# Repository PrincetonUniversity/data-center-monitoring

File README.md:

# A Wired Sensing Suite for Data Center Climate Monitoring

This repository contains all files related to the data center climate sensing/monitoring project built as independent work under Prof. David Wentzlaff <<wentzlaf@princeton.edu>>.

Work on this project was conducted by:

 - [Ryan O'Shea '16](http://ryanoshea.com) <<roshea@princeton.edu>> (2015-16)
 - Felix Madutsa '18 <<fmadutsa@princeton.edu>> (2015)
 - Peter de Groot '15
 - Rahul Subramanian '14
 
**For a full breakdown of the project, see the [report](/report-roshea/O'Shea_Ryan_Thesis.pdf).**

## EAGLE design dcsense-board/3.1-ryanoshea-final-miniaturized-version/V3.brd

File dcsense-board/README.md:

# Sensor Board

The `dcsense` PCB is the sensing component of the system. It is a small PCB with a TI TMP175 digital temperature sensor, DIP switches for configuring the sensor's I<sup>2</sup>C address, and a header for connecting the board to a ribbon cable via a connector. Other features include a power indicator LED and 2 decoupling capacitors.

## Layout

Reproduced below without copper pours for visibility.

## Schematic

## Addressing

The 6 switches are used to configure the address of the sensor on the bus. Beacause the switches control only 3 address pins on the TMP175 sensor (using trinary logic), not all configurations of switches will produce valid addresses. Two switches are used to configure one pin. Each pair of switches can only be set to a certain combination of values. Those pairs are (from left to right) 1 and 4, 2 and 5, 3 and 6. For a given pair of switches, the only restriction is that **both switches can't be ON simultaneously**. This is because for each pair, one switch pulls the address pin to GND and one pulls it up to V<sub>DD</sub>. Leaving both switches OFF allows the voltage of the pin to float, which a third valid option (hence trinary logic). Having both switches ON creates a voltage divider and provides a steady voltage of V<sub>DD</sub>/2 to the pin, which causes undefined behavior (and creates a leakage current that will waste unnecessary power). 

The valid address configurations are listed here, along with the decimal address values they correspond to: \[[JSON](/dcsense-board/3.1-ryanoshea-final-miniaturized-version/address-map.json)\]\[[Excel](/dcsense-board/3.1-ryanoshea-final-miniaturized-version/address-map.xlsx)\]

## History

The 3 major versions of the board are shown below.

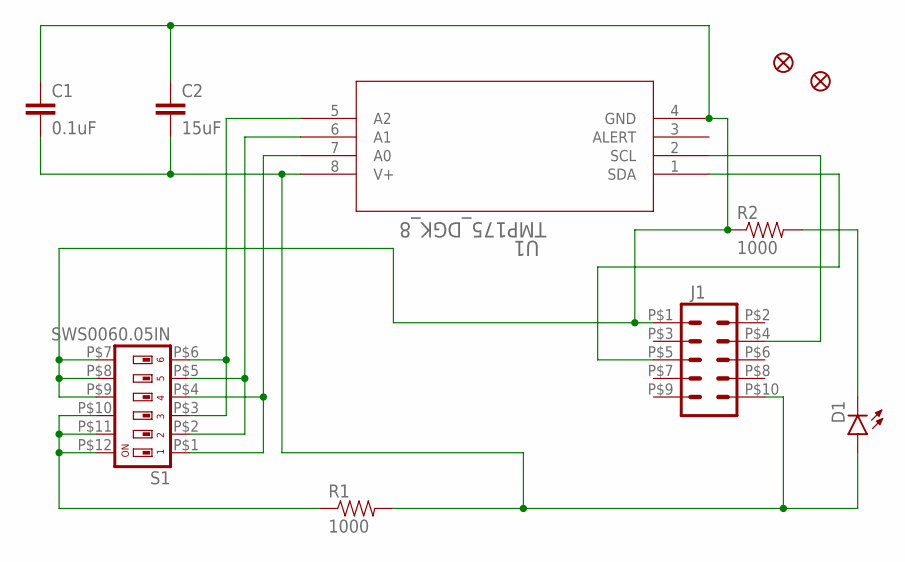
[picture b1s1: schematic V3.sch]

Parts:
C1: 0.1uF; 0805
C2: 15uF; 0805
D1: LED-BLUE1206; LED-1206
FID1, FID3: FIDUCIAL1X2; FIDUCIAL-1X2
J1: M05X22X5-UNSHROUDED_SMD; 2X5-UNSHROUDED_SMD
R1, R2: 1000; 0805
S1: SWS0060.05IN; SMS-006
U1: TMP175_DGK_8; DGK8

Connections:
A1: S1.P$2 (2), S1.P$5 (5), U1.6 (A1)
A2: S1.P$3 (3), S1.P$6 (6), U1.5 (A2)
GND: C1.1, C2.1, J1.P$1 (1), R2.1, S1.P$7 (7), S1.P$8 (8), S1.P$9 (9), U1.4 (GND)
unnamed: R1.1, S1.P$10 (10), S1.P$11 (11), S1.P$12 (12)
unnamed: S1.P$1 (1), S1.P$4 (4), U1.7 (A0)
unnamed: D1.C, R2.2
POWER: C1.2, C2.2, D1.A, J1.P$10 (10), R1.2, U1.8 (V+)
SCL: J1.P$4 (4), U1.2 (SCL)
SDA: J1.P$5 (5), U1.1 (SDA)

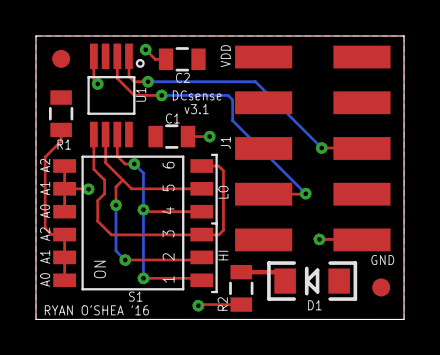
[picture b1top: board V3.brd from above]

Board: 2 copper layers, 20.4 x 15.7 mm, 10 parts (0 on the bottom side), 9 nets.

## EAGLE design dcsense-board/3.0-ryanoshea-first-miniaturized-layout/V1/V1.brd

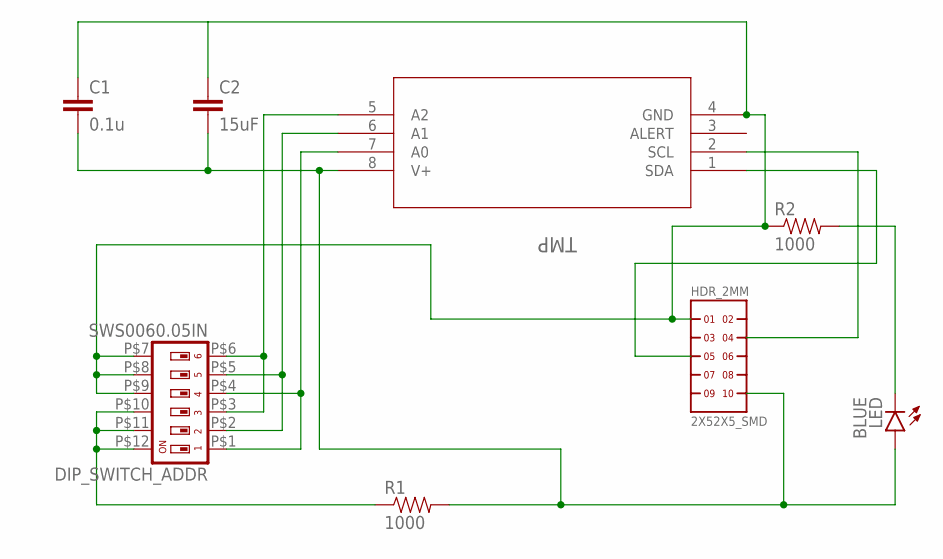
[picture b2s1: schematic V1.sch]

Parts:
C1: 0.1u; 0805
C2: 15uF; 0805-CAP
DIP_SWITCH_ADDR: SWS0060.05IN; SMS-006
HDR_2MM: 2X52X5_SMD; 2X5
LED: BLUE; LED-1206
R1, R2: 1000; 0805
TMP: TMP175_DGK_8; DGK8

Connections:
A1: DIP_SWITCH_ADDR.P$2 (2), DIP_SWITCH_ADDR.P$5 (5), TMP.6 (A1)
A2: DIP_SWITCH_ADDR.P$3 (3), DIP_SWITCH_ADDR.P$6 (6), TMP.5 (A2)
GND: C1.1, C2.1, DIP_SWITCH_ADDR.P$7 (7), DIP_SWITCH_ADDR.P$8 (8), DIP_SWITCH_ADDR.P$9 (9), HDR_2MM.P$1 (1), R2.1, TMP.4 (GND)
unnamed: C1.2, C2.2, HDR_2MM.P$10 (10), LED.A, R1.2, TMP.8 (V+)
unnamed: DIP_SWITCH_ADDR.P$10 (10), DIP_SWITCH_ADDR.P$11 (11), DIP_SWITCH_ADDR.P$12 (12), R1.1
unnamed: DIP_SWITCH_ADDR.P$1 (1), DIP_SWITCH_ADDR.P$4 (4), TMP.7 (A0)
unnamed: LED.C, R2.2
SCL: HDR_2MM.P$4 (4), TMP.2 (SCL)
SDA: HDR_2MM.P$5 (5), TMP.1 (SDA)

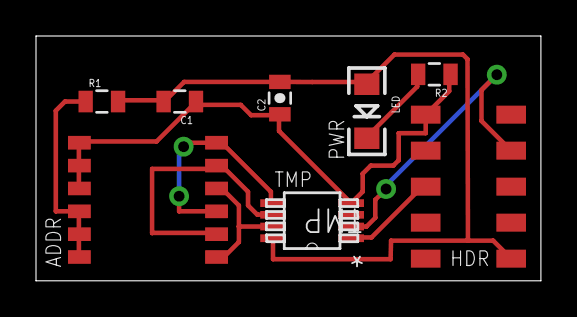
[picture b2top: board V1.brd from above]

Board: 2 copper layers, 28.1 x 13.6 mm, 8 parts (0 on the bottom side), 9 nets.

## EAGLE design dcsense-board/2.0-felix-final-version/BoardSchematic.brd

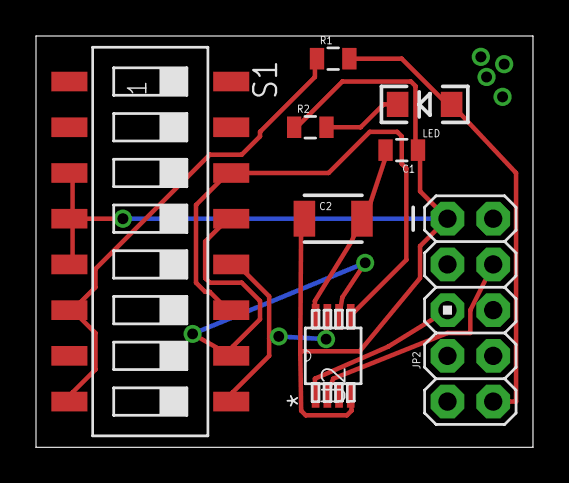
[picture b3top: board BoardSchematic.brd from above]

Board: 2 copper layers, 27.6 x 22.8 mm, 8 parts (0 on the bottom side), 10 nets.

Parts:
C1: 0.1micro; 0805
C2: 1micro; 1210
JP2: AVR_ICSP
LED: BLUE; LED-1206
R1, R2: 1000; 0805
S1: SWS008; SMS-008
U2: TMP175_DGK_8; DGK8

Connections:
unnamed: C1.2, C2.2, U2.8
unnamed: JP2.4, U2.2
unnamed: C1.1, C2.1, JP2.1, R2.1, S1.3, S1.4, S1.5, U2.4
unnamed: R1.1, S1.6, S1.8
unnamed: S1.10, S1.13, U2.6
unnamed: S1.9, S1.12, U2.7
unnamed: S1.11, S1.14, U2.5
unnamed: LED.C, R2.2
unnamed: JP2.10, LED.A, R1.2
unnamed: JP2.5, U2.1

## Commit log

2016-02-24 Init
2016-02-24 Added Felix's beaglebone python files
2016-02-24 Removed calls to DB, added print statements for temp readings
2016-02-24 Added interim report
2016-02-24 Added README
2016-02-24 Added board files from recent versions
2016-02-24 Some .gitignore changes
2016-02-24 Ignored PyCharm files
2016-02-24 Organized beaglebone controller code into old and new projects
2016-03-07 Updated board silkscreens
2016-03-17 Lockfiles
2016-03-17 Added new, simplified BeagleBone code
2016-03-17 [BB] Added error handling; added data transmission to server
2016-03-17 [Server] Added basic server to accept sensor data
2016-03-17 [Server] Added received readings tally for convenience
2016-03-17 [BB] Fixed bus 2 errors, decreased time resolution
    Also fixed error handling bugs
2016-03-18 [Server][BB] Starting saving readings to db
2016-03-18 [BRD] Fixed reference designator for header in BoM
2016-03-21 [Server] Established working server for backend and frontend
2016-03-22 [Server] Added AngularJS app with full authentication, added authentication functionality to Node server
    Built new blank AngularJS application:
    - Functional login page
    - Promise-based route authentication
    - Persistent user sessions via cookies
    - Server side authentication, with managed user DB
    - Admin page with new user registration form
2016-03-22 [Server] Fixed JSON parsing bug on logout requests
2016-03-22 Edited unix file permissions for server
2016-03-22 [Server] Added basic splash page
2016-03-23 [BB][Server] Updated controller code to send data to production server
2016-03-23 [BB] Added exception handler for failed fork()
    This solution just ignores the error. If it happens frequently, it'll
    need to be addressed a different way to avoid lost readings.
2016-03-23 [Server] Moved logout function to a directive
    So it can be used on each page without having to define a
    $scope.logout() for each page that needs a login page.
2016-03-23 [Server] Added empty dashboard page
    Made the dashboard the default page for a logged-in user
2016-03-23 [BB] Fixed issue where each bus got different timestamp
2016-03-23 [BB] Fixed issue where child processes became zombies
2016-03-24 [Server] Added some API handlers for getting readings
2016-03-26 [Server] Added working user access levels
2016-03-26 [Server] Broke out session status check to separate function
2016-03-26 [Server] Restructured session status callback to only be called if user is authorized
2016-03-26 [Server] Added authentication to one data request handler
2016-03-27 [Server] Added authentication to all requests for sensor data
2016-03-27 [Server] Added facilities & tool for managing facility owners
2016-03-28 [Server] Fixed bug allowing modifying owners on unselected facility
2016-03-28 [Server] Added admin tool to delete users
2016-03-28 [Server] Added Node.js package.json
2016-03-28 [Server] Added server app readme
2016-03-30 [Server] Limited user access to data based on facility ownership
    - Sensor data requests now check for ownership, and requests to list
    facilities return only those a user is owner of (or all if user is
    admin)
    - Added admin tool to link controllers to facilities
    - Added first parts dashboard
2016-03-30 [Server] Added code to fetch available dates for a controller on the dash
2016-03-30 [Server] Implemented readings fetching by date slider
2016-03-30 [Server] Added every-10-mins collection for readings
2016-03-30 [Server] Fixed typo
2016-03-30 [Server] Possibly fixed ReadingCounter incrementing bug
2016-03-30 [Server] Commented each server function
2016-03-30 [BB] Removed old controller code for simplicity
2016-04-02 [Server] Server header
2016-04-02 [Server] Fixed date slider on mobile
2016-04-02 [Server] Dash: facility and controller selection
2016-04-03 [Server] Tooltips and early controller name editing support
2016-04-03 [Server] Added controller renaming
2016-04-03 [Sever] Added dcsense board switch-to-address mappings
2016-04-03 [BB] Changed method to grab MAC address
2016-04-03 [Server] Accommodations for string-based MAC address
2016-04-04 [Server] Small tweaks to frontend
2016-04-04 [Server] Fixed controller removal from facility bug
    Also added beginnings of support for controller cabinet width
2016-04-04 [Server] Added controller width editing
    Also modified API to provide more general controller update
    functionality (will be useful in the future).
2016-04-04 [Server] Made controller editing non-destructive
2016-04-04 [Server] Added readings table & display mode tabs
2016-04-05 [Server] Date slider styling
2016-04-05 [Server] Visual updates to dashboard page
2016-04-05 [Server] Fixed timezone offset bug
2016-04-05 [Server] Added registration to login page
2016-04-05 [Server] Improved login/signup buttons
2016-04-06 [BB] Ignored VS Code IDE files
2016-04-06 [Server] Fixed controller <select> default issue
2016-04-06 [Server] Added IP logging for readings submission
2016-04-06 [Server] Cabinets now store sensor layout mapping; frontend now graphically displays those representations
    No tool yet to actually map sensors to particular locations, but
    framework exists for it.
2016-04-09 [Server] Added barebones sensor mapping tool
2016-04-11 [Server] Better sensor mapping editor interface
2016-04-11 [Server] Added basic sensor data graphing
2016-04-11 [Server] Fixed duplicate graphs when switching sensor
2016-04-11 [Sensor] Added selected sensor indicator
2016-04-11 [Server] Fixed graphs displaying time-reversed values
2016-04-11 [Server] Added high temperature alert view
2016-04-11 [Server] Added basic full data export
    Needs to be changed to be limited by facility, and to provide options
    for date ranges
2016-04-11 [Server] Exported readings now come from Readings collection
    ResearchReadings collection is too large to handle exporting
2016-04-12 [Server] Added bootstrap datepicker
2016-04-12 [Server] Started displaying address info when editing mappings
2016-04-12 [Server] Sensor mapping editor display bug
2016-04-12 [Server] Hid sensor graph by default, enable hiding graph
2016-04-12 [Server] Added date range to export tool
2016-04-12 [Server] Export limited to facility's controllers
2016-04-12 [Server] Fixed facility selector styling
2016-04-12 [Server] Added refresh button to dashboard
2016-04-12 [Server] Tooltip tweak
2016-04-12 [Server] Added loading indicator for export tool
2016-04-12 [Server] Added page titles
2016-04-12 [Server] Frontend now waits to render until angular is initialized
2016-04-12 [Server] Graphs now get cleared when changing facility or controller
2016-04-12 [Server] Fixed graph taking up space after being cleared
2016-04-14 [BB] Added BeagleBone readme
2016-04-14 [Server] Now using remote mongodb endpoint
2016-04-14 [Server] Server can now run with local and prod DBs
2016-04-14 [Server] High temperature alerts can now be filtered by date
2016-04-14 [Server] Clicking a sensor in a table displays that sensor in cabinet view
2016-04-14 [Server] Updated server readme to reflect new MongoDB configuration
2016-04-15 [BB] Added schematic for BB Cape
2016-04-15 Ignored Eagle lock files
2016-04-15 [BB] Added cape schematic image
2016-04-15 Eagle cleanup
2016-04-15 [BB] Added readme for BeagleBone cape schematic
2016-04-15 [Server] Improvements to clicking rows in table view
2016-04-15 [BB] BeagleBones now send any errors to server
2016-04-15 [BB] Improved error logging
2016-04-16 [BB] Fixed syntax error
2016-04-16 [BB][Server] Fixing errors in readings transmission
2016-04-16 [Server] Fixed error processing incoming readings
2016-04-16 [Server] Fixed bug where controllers were unnecessarily changed
2016-04-16 [Report] Added some board photos
2016-04-16 [BB] Updated cape schematic w/ real resistors
2016-04-16 [BB] Added cape photo to readme
2016-04-17 [BB] Updated sensor board readme
2016-04-17 [BB] Added schematic to sensor board readme
2016-04-17 [BB] bitmap sensor-board schematic
2016-04-17 [BB] Same as last commit
2016-04-17 [Server] Added navbar
2016-04-17 [Server] Color tweak
2016-04-17 [Server] Fixed issue where graph would collapse horizontally after export
2016-04-17 [Server] Fixed export tool for non-admins
2016-04-19 [Report] Updated lots of figures
2016-04-19 [Server] Updated broken facility deleted message
2016-04-19 [Server] Changed line graph color
2016-04-21 [Report] More assets
2016-04-21 [BB] Configured request to go through proxy
2016-04-21 Revert "[BB] Configured request to go through proxy"
    This reverts commit 49809e4507e91491be8bd2739193c54c67e198bd.
2016-04-21 [BB] Started printing number of readings to stdout
2016-04-21 [Server] Started timestamping sensor data server-side
2016-04-21 [Server] Spots on server rack without mapped sensors can no longer be clicked
2016-04-22 [Server] Added custom favicon
2016-04-22 [Server] Added about page
2016-04-22 [Server] Added links to about page
2016-04-22 [Server] Added text explaining sensor graph
2016-04-22 [Report] More figures and report work
2016-04-25 [BB] Fixed some incorrect comments
2016-04-25 [BB] Style
2016-04-25 [BB} Style
2016-04-26 [Report] Created sample plots and updated figures
2016-04-27 [BB] Updated cape schematic
    - All unused wires are now grounded
    - I2C pull-up resistor values decreased
    - Used another pair of 4.7KΩ resistors in parallel with the built-in
    I2C2 pull-ups, making the total pull-up resistance 2.35KΩ
    - Reduced I2C1 pull-ups to the closest available value to 2.35KΩ which
    is, 2.2KΩ
2016-04-27 [Server] Fixed new user registration flow
2016-04-28 [Report] Downsized DSLR images for report
2016-04-28 [Server] Added CC credit for login page background
2016-04-29 [Report] Figure and bib updates
2016-05-02 [Report] Updated dash screenshot to use an HPCRC rack
2016-05-02 [Report] Added final senior thesis
    Also some reorganization
2016-05-02 [Report] Pointed readme to thesis pdf
2016-05-09 Fixed cape image linking
2016-05-09 Updated image links

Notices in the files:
parts and their libraries:
SparkFun-Capacitors: Licensing: Creative Commons ShareAlike 4.0 International - https://creativecommons.org/licenses/by-sa/4.0
